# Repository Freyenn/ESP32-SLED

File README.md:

## Kicad Project for SLED ESP32 Development Board
Feel Free to Fork this repo

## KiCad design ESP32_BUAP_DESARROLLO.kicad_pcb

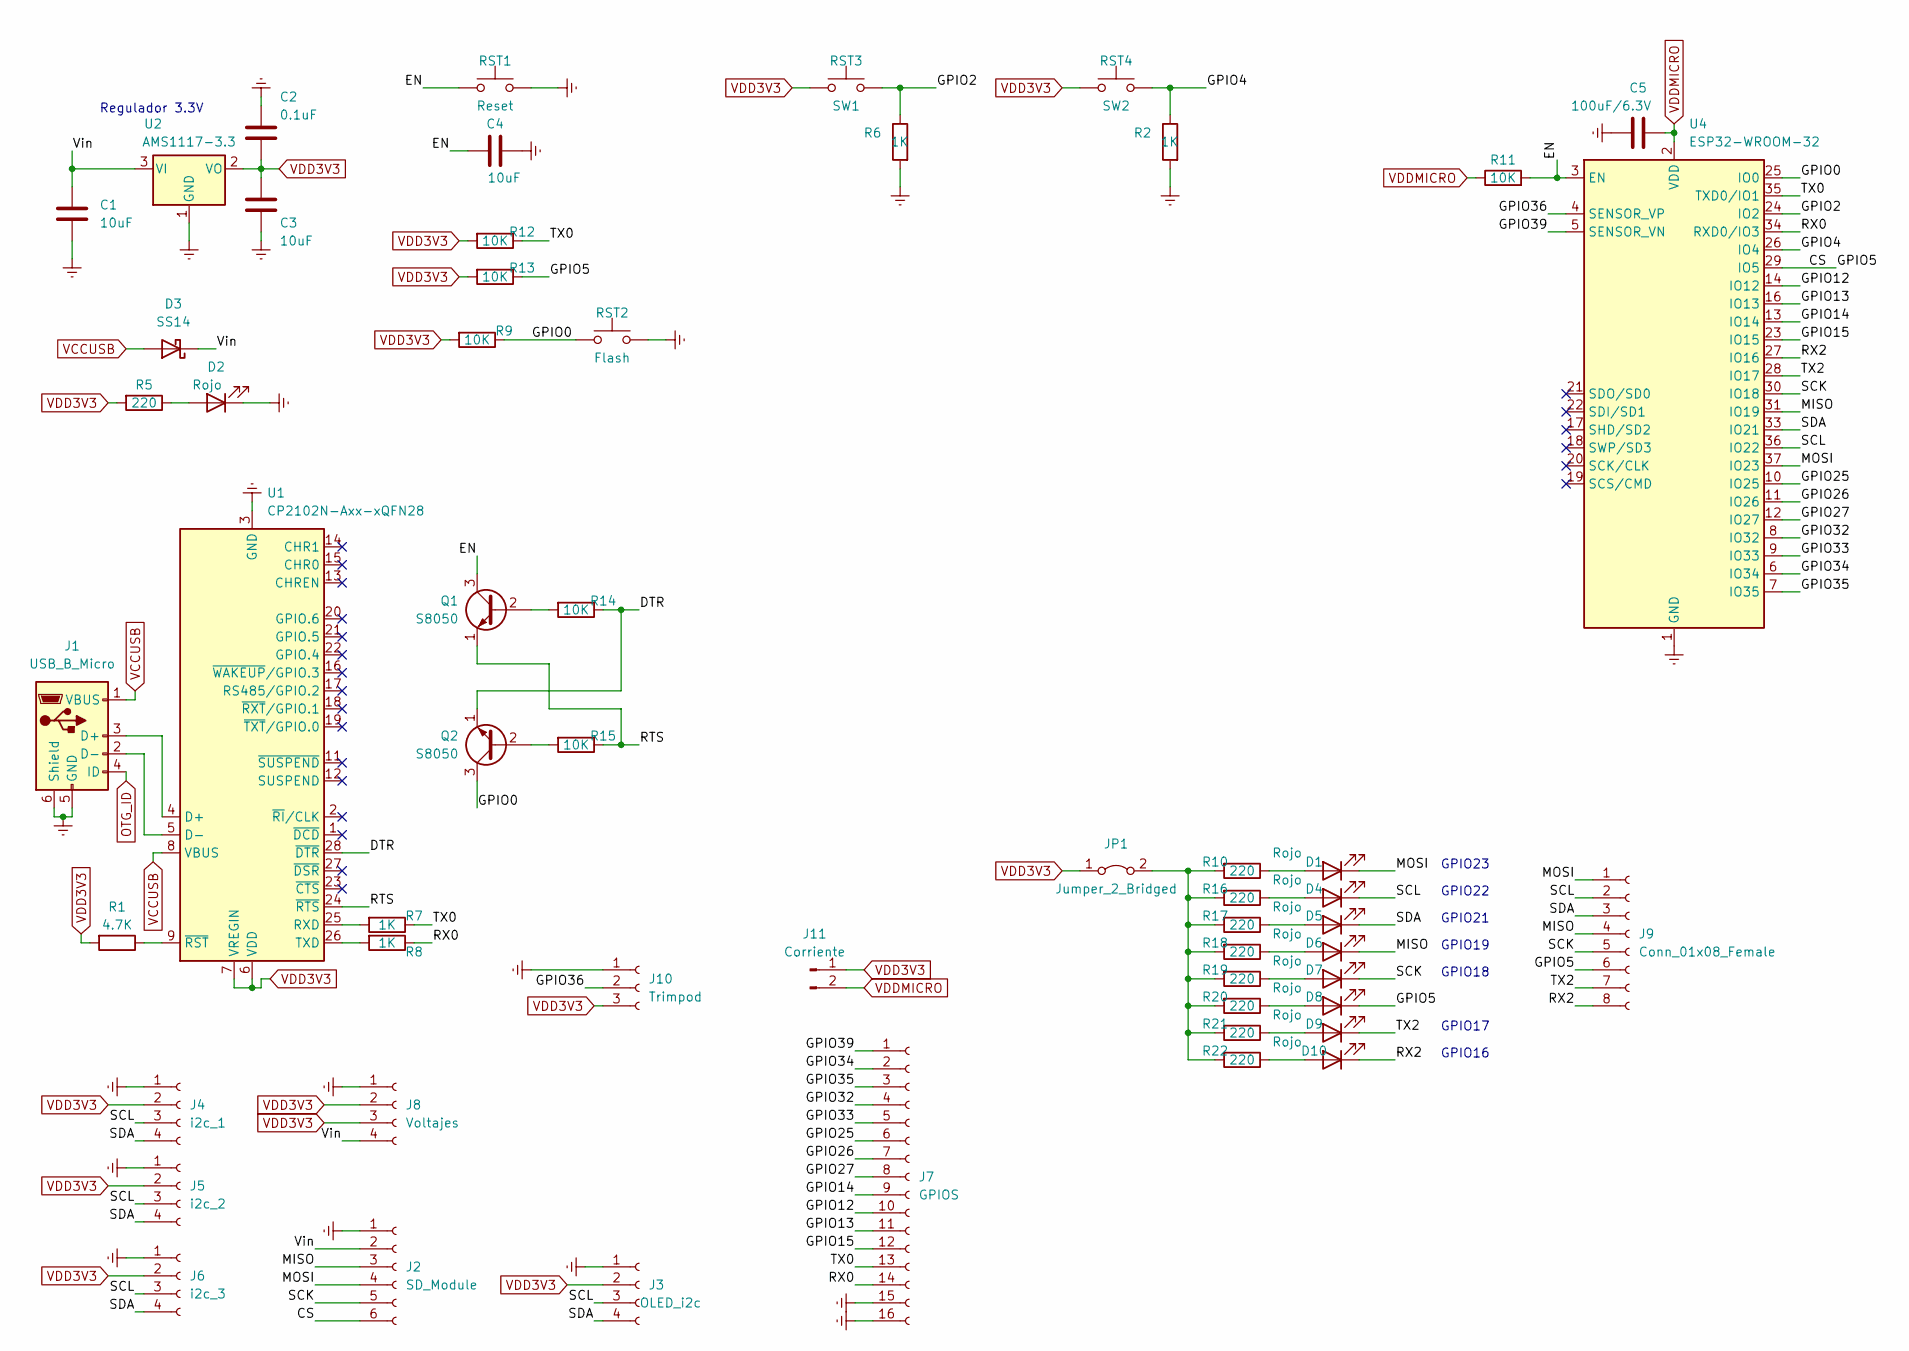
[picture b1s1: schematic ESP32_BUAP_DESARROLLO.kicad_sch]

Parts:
C1, C3: 10uF; C_1210_3225Metric_Pad1.33x2.70mm_HandSolder
C2: 0.1uF; C_0805_2012Metric_Pad1.18x1.45mm_HandSolder
C4: 10uF; C_0805_2012Metric_Pad1.18x1.45mm_HandSolder
C5: 100uF/6.3V; C_1210_3225Metric_Pad1.33x2.70mm_HandSolder
D1, D2, D4, D5, D6, D7, D8, D9, D10: Rojo; LED_0805_2012Metric_Pad1.15x1.40mm_HandSolder
D3: SS14; D_SMA
J1: USB_B_Micro; USB_Mini-B_Lumberg_2486_01_Horizontal
J2: SD_Module; PinSocket_1x06_P2.54mm_Vertical
J3: OLED_i2c; PinSocket_1x04_P2.54mm_Vertical
J4: i2c_1; PinSocket_1x04_P2.54mm_Vertical
J5: i2c_2; PinSocket_1x04_P2.54mm_Vertical
J6: i2c_3; PinSocket_1x04_P2.54mm_Vertical
J7: GPIOS; PinSocket_1x16_P2.54mm_Vertical
J8: Voltajes; PinSocket_1x04_P2.54mm_Vertical
J9: Conn_01x08_Female; PinSocket_1x08_P2.54mm_Vertical
J10: Trimpod; PinSocket_1x03_P2.54mm_Vertical
J11: Corriente; PinHeader_1x02_P2.54mm_Vertical
JP1: Jumper_2_Bridged; PinHeader_1x02_P2.54mm_Vertical
Q1, Q2: S8050; SOT-23
R1: 4.7K; R_0603_1608Metric_Pad0.98x0.95mm_HandSolder
R2, R6, R7, R8: 1K; R_0603_1608Metric_Pad0.98x0.95mm_HandSolder
R5, R10, R16, R17, R18, R19, R20, R21, R22: 220; R_0603_1608Metric_Pad0.98x0.95mm_HandSolder
R9, R11, R12, R13, R14, R15: 10K; R_0603_1608Metric_Pad0.98x0.95mm_HandSolder
RST1: Reset; SW_SPST_B3U-1000P
RST2: Flash; SW_SPST_B3U-1000P
RST3: SW1; SW_SPST_CK_RS282G05A3
RST4: SW2; SW_SPST_CK_RS282G05A3
U1: CP2102N-Axx-xQFN28; QFN-28-1EP_5x5mm_P0.5mm_EP3.35x3.35mm
U2: AMS1117-3.3; SOT-223-3_TabPin2
U4: ESP32-WROOM-32

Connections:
/CS: D8.1 (K), J2.6, J9.6, R13.1, U4.29 (IO5)
/DTR: Q2.1 (E), R14.1, U1.28 (~DTR)
/EN: C4.1, Q1.3 (C), R11.2, RST1.1, U4.3 (EN)
/GPIO0: Q2.3 (C), R9.1, RST2.1, U4.25 (IO0)
/GPIO2: R6.1, RST3.1, U4.24 (IO2)
/GPIO4: R2.1, RST4.1, U4.26 (IO4)
/GPIO12: J7.10, U4.14 (IO12)
/GPIO13: J7.11, U4.16 (IO13)
/GPIO14: J7.9, U4.13 (IO14)
/GPIO15: J7.12, U4.23 (IO15)
/GPIO25: J7.6, U4.10 (IO25)
/GPIO26: J7.7, U4.11 (IO26)
/GPIO27: J7.8, U4.12 (IO27)
/GPIO32: J7.4, U4.8 (IO32)
/GPIO33: J7.5, U4.9 (IO33)
/GPIO34: J7.2, U4.6 (IO34)
/GPIO35: J7.3, U4.7 (IO35)
/GPIO36: J10.2, U4.4 (SENSOR_VP)
/GPIO39: J7.1, U4.5 (SENSOR_VN)
/MISO: D6.1 (K), J2.3, J9.4, U4.31 (IO19)
/MOSI: D1.1 (K), J2.4, J9.1, U4.37 (IO23)
/RTS: Q1.1 (E), R15.1, U1.24 (~RTS)
/RX0: J7.14, R8.1, U4.34 (RXD0/IO3)
/RX2: D10.1 (K), J9.8, U4.27 (IO16)
/SCK: D7.1 (K), J2.5, J9.5, U4.30 (IO18)
/SCL: D4.1 (K), J3.3, J4.3, J5.3, J6.3, J9.2, U4.36 (IO22)
/SDA: D5.1 (K), J3.4, J4.4, J5.4, J6.4, J9.3, U4.33 (IO21)
/TX0: J7.13, R7.1, R12.1, U4.35 (TXD0/IO1)
/TX2: D9.1 (K), J9.7, U4.28 (IO17)
/Vin: C1.1, D3.1 (K), J2.2, J8.4, U2.3 (VI)
Earth: C1.2, C2.1, C3.2, C4.2, C5.1, D2.1 (K), J1.5 (GND), J1.6 (Shield), J2.1, J3.1, J4.1, J5.1, J6.1, J7.15, J7.16, J8.1, J10.1, R2.2, R6.2, RST1.2, RST2.2, U1.3 (GND), U1.29 (GND), U2.1 (GND), U4.1 (GND), U4.15 (GND), U4.38 (GND), U4.39 (GND)
unnamed: D1.2 (A), R10.1
unnamed: D2.2 (A), R5.1
unnamed: D4.2 (A), R16.1
unnamed: D5.2 (A), R17.1
unnamed: D6.2 (A), R18.1
unnamed: D7.2 (A), R19.1
unnamed: D8.2 (A), R20.1
unnamed: D9.2 (A), R21.1
unnamed: D10.2 (A), R22.1
unnamed: J1.2 (D-), U1.5 (D-)
unnamed: J1.3 (D+), U1.4 (D+)
unnamed: JP1.2 (B), R10.2, R16.2, R17.2, R18.2, R19.2, R20.2, R21.2, R22.2
unnamed: Q1.2 (B), R14.2
unnamed: Q2.2 (B), R15.2
unnamed: R1.1, U1.9 (~RST)
unnamed: R7.2, U1.25 (RXD)
unnamed: R8.2, U1.26 (TXD)
OTG_ID: J1.4 (ID)
VCCUSB: D3.2 (A), J1.1 (VBUS), U1.8 (VBUS)
VDD3V3: C2.2, C3.1, J3.2, J4.2, J5.2, J6.2, J8.2, J8.3, J10.3, J11.1, JP1.1 (A), R1.2, R5.2, R9.2, R12.2, R13.2, RST3.2, RST4.2, U1.6 (VDD), U1.7 (VREGIN), U2.2 (VO)
VDDMICRO: C5.2, J11.2, R11.1, U4.2 (VDD)

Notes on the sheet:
GPIO21
GPIO16
GPIO23
Regulador 3.3V
GPIO18
GPIO22
GPIO19
GPIO17

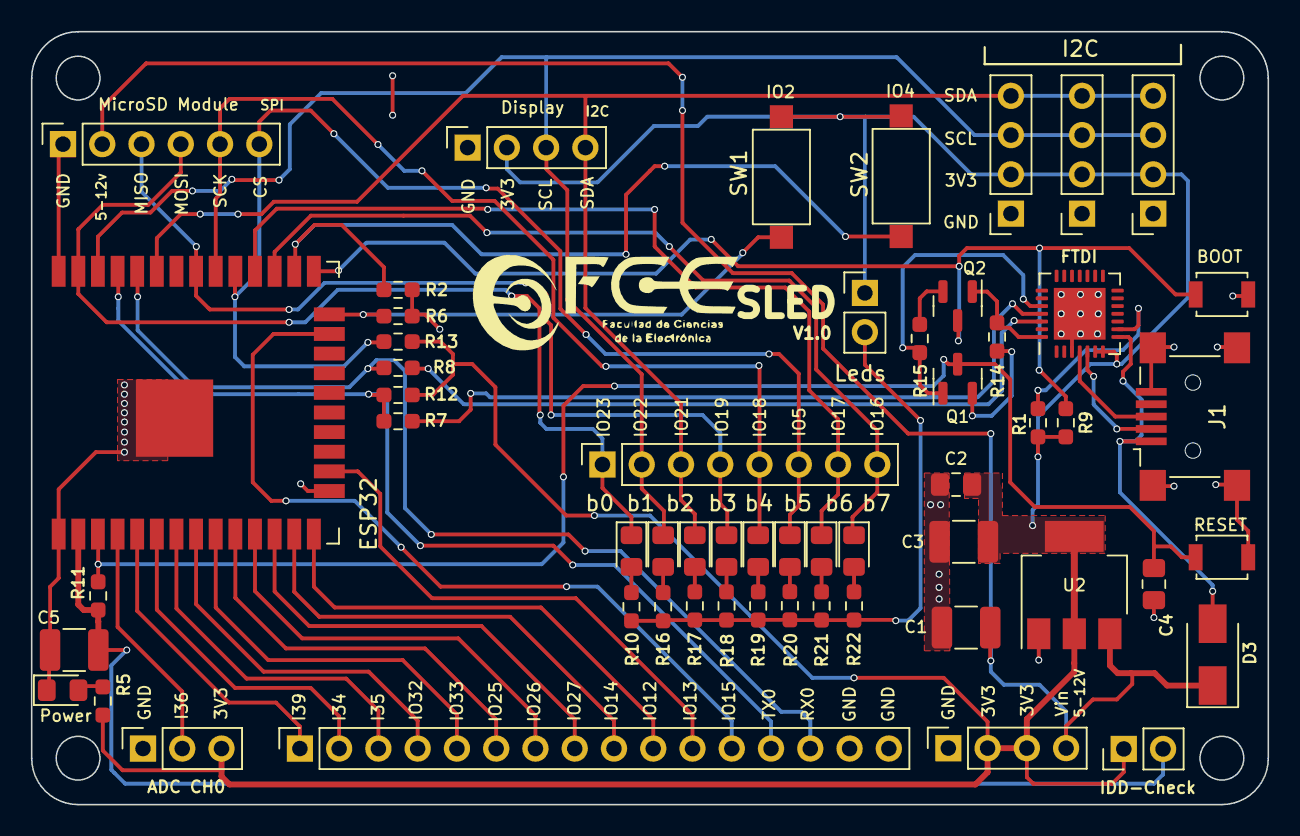
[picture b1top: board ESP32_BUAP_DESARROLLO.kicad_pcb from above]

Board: 2 copper layers, 80.0 x 50.0 mm, 56 parts (0 on the bottom side), 51 nets.

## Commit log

2022-11-23 add README.md
